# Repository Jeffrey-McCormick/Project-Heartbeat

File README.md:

Hello! Welcome to Project Heartbeat, my individual project for my ENGR 355 - Embedded System Design class.
This project's first revision is finished and turned in for credit. Later versions may appear as I have opportunity to expand this heartrate monitor's capabilities. I used KiCad and ARM Keil applications for designing and programming the board. 

I encourage you to read the Project Heartbeat Design Report to understand my design approach as well as what the functions of my code are for. 
Although, you should be able to read the comments in my code and understand what is happening. 

Here is what it looked like in KiCad and in reality.

The text I used was produced by ARM Education. Here is the Github resource: https://github.com/arm-education/Embedded-Systems-Fundamentals?tab=readme-ov-file

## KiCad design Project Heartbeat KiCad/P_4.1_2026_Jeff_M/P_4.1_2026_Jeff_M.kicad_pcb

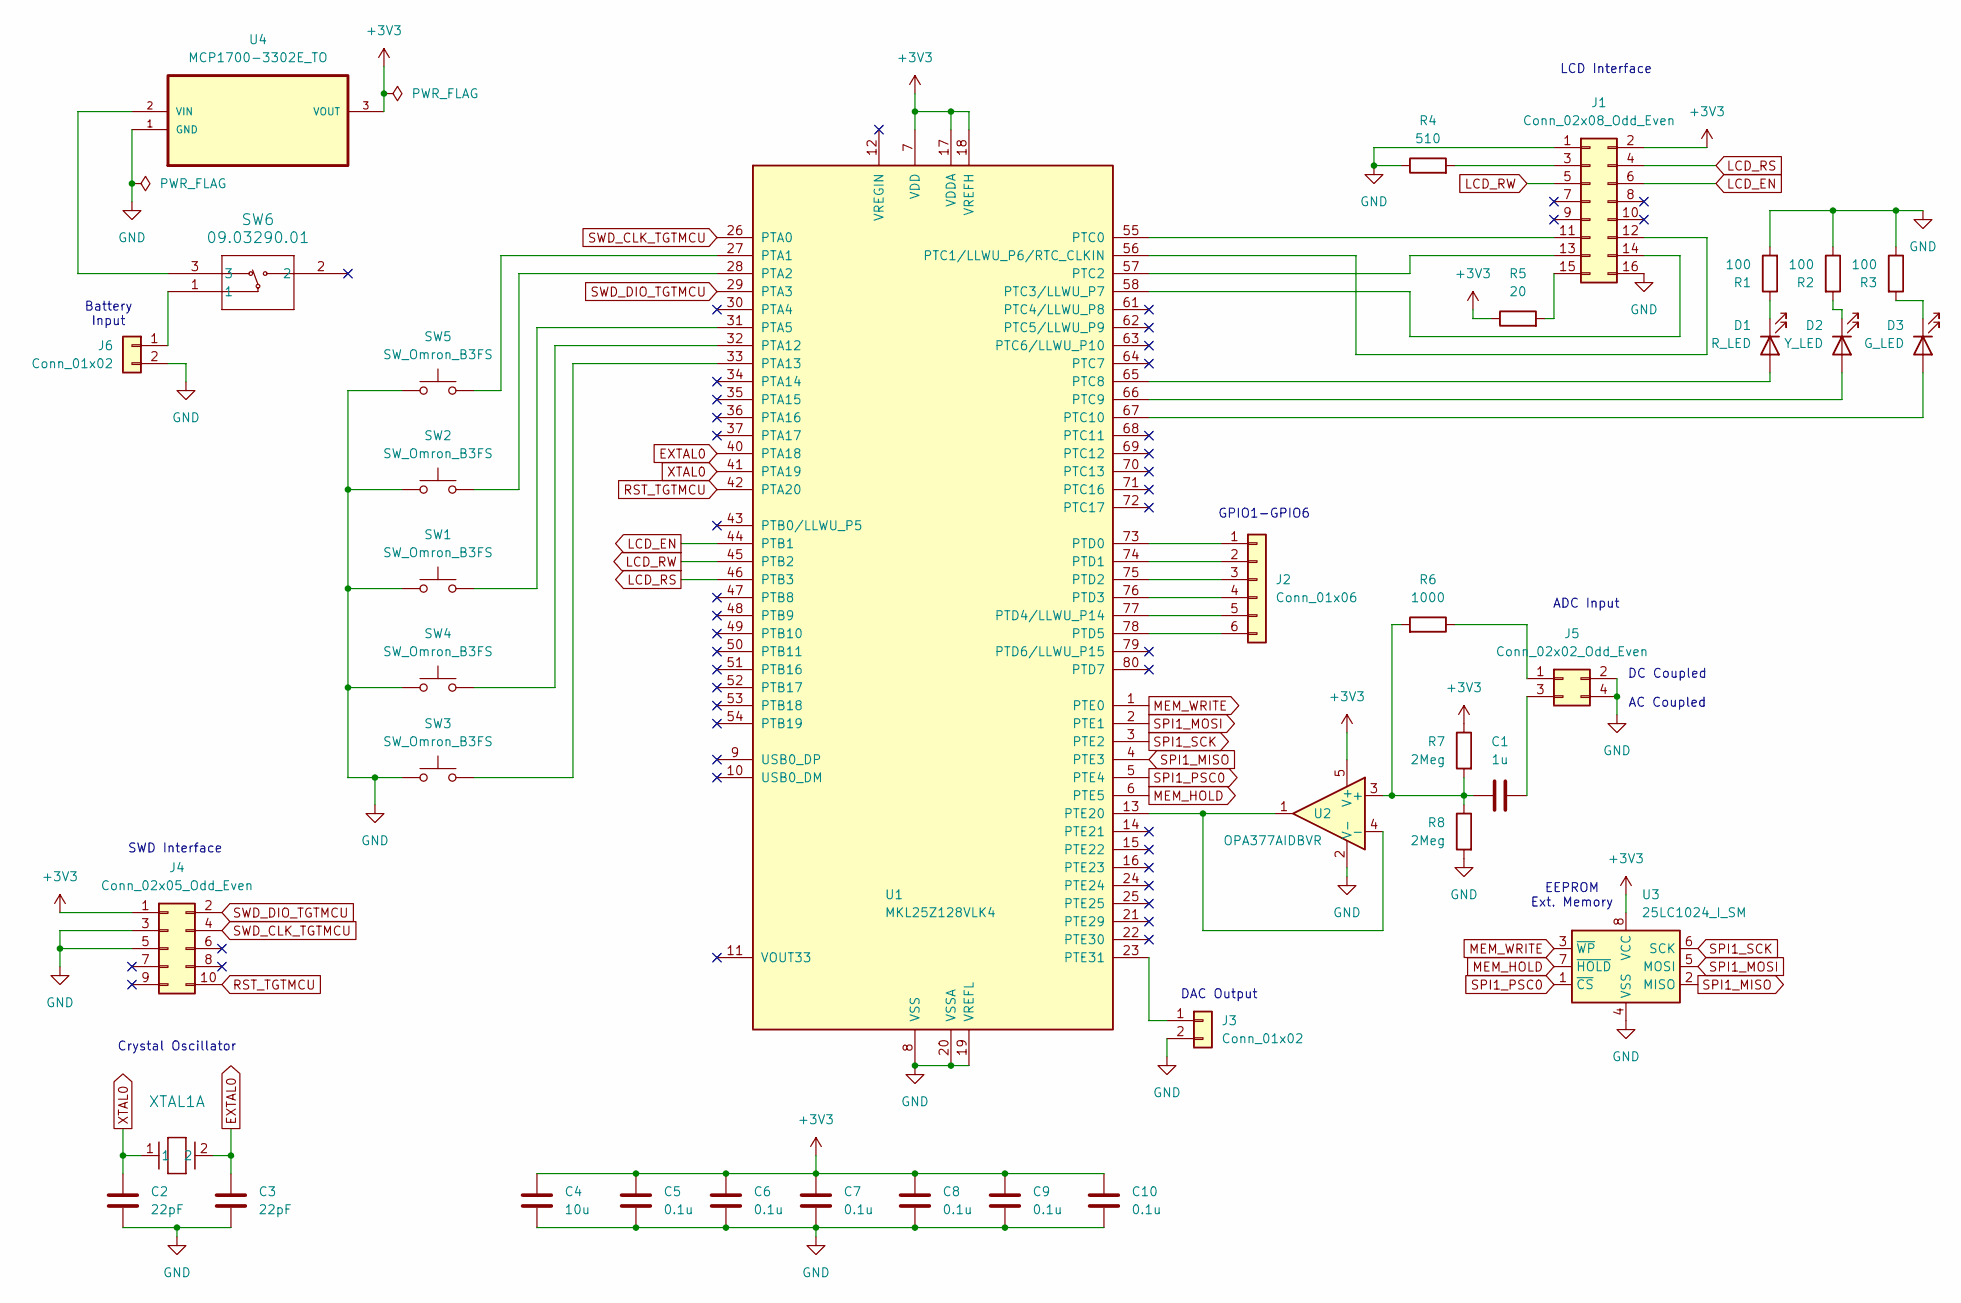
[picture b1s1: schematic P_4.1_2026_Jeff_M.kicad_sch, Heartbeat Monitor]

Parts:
C1: 1u; C_0805_2012Metric
C2, C3: 22pF; C_0805_2012Metric
C4: 10u; C_0805_2012Metric
C5, C6, C7, C8, C9, C10: 0.1u; C_0805_2012Metric
D1: R_LED; LED_1206_3216Metric
D2: Y_LED; LED_1206_3216Metric
D3: G_LED; LED_1206_3216Metric
J1: Conn_02x08_Odd_Even; PinHeader_2x08_P2.54mm_Vertical
J2: Conn_01x06; PinHeader_1x06_P2.54mm_Vertical
J3, J6: Conn_01x02; PinHeader_1x02_P2.54mm_Vertical
J4: Conn_02x05_Odd_Even; PinHeader_2x05_P1.27mm_Vertical
J5: Conn_02x02_Odd_Even; PinHeader_2x02_P2.54mm_Vertical
R1, R2, R3: 100; R_0805_2012Metric
R4: 510; R_0805_2012Metric
R5: 20; R_0805_2012Metric
R6: 1000; R_0805_2012Metric
R7, R8: 2Meg; R_0805_2012Metric
SW1, SW2, SW3, SW4, SW5: SW_Omron_B3FS; SW_SPST_Omron_B3FS-101xP
SW6: 09.03290.01; 09.03290_EAO
U1: MKL25Z128VLK4; LQFP-80_12x12mm_P0.5mm
U2: OPA377AIDBVR; SOT95P280X145-5N
U3: 25LC1024_I_SM; SOIC127P794X202-8N
U4: MCP1700-3302E_TO; TO127P254X495-3; MPN MCP1700-3302E/TO
XTAL1: ABM3-8.000MHZ-D2Y-T; XTAL_ABM3-8.000MHZ-D2Y-T_ABR

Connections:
+3V3: C4.1, C5.1, C6.1, C7.1, C8.1, C9.1, C10.1, J1.2, J4.1, R5.1, R7.1, U1.7 (VDD), U1.17 (VDDA), U1.18 (VREFH), U1.38 (VDD), U1.60 (VDD), U2.5 (V+), U3.8 (VCC), U4.3 (VOUT)
EXTAL0: C3.1, U1.40 (PTA18), XTAL1.2
GND: C2.2, C3.2, C4.2, C5.2, C6.2, C7.2, C8.2, C9.2, C10.2, J1.1, J1.16, J3.2, J4.3, J4.5, J5.2, J5.4, J6.2, R1.2, R2.1, R3.1, R4.1, R8.2, SW1.1, SW2.1, SW3.1, SW4.1, SW5.1, U1.8 (VSS), U1.19 (VREFL), U1.20 (VSSA), U1.39 (VSS), U1.59 (VSS), U2.2 (V-), U3.4 (VSS), U4.1 (GND)
LCD_EN: J1.6, U1.44 (PTB1)
LCD_RS: J1.4, U1.46 (PTB3)
LCD_RW: J1.5, U1.45 (PTB2)
MEM_HOLD: U1.6 (PTE5), U3.7 (~HOLD)
MEM_WRITE: U1.1 (PTE0), U3.3 (~WP)
unnamed: D1.2 (A), U1.65 (PTC8)
unnamed: D1.1 (K), R1.1
unnamed: D2.2 (A), U1.66 (PTC9)
unnamed: D2.1 (K), R2.2
unnamed: D3.2 (A), U1.67 (PTC10)
unnamed: D3.1 (K), R3.2
unnamed: J1.3, R4.2
unnamed: J1.11, U1.55 (PTC0)
unnamed: J1.12, U1.56 (PTC1/LLWU_P6/RTC_CLKIN)
unnamed: J1.13, U1.57 (PTC2)
unnamed: J1.14, U1.58 (PTC3/LLWU_P7)
unnamed: J1.15, R5.2
unnamed: J2.1, U1.73 (PTD0)
unnamed: J2.2, U1.74 (PTD1)
unnamed: J2.3, U1.75 (PTD2)
unnamed: J2.4, U1.76 (PTD3)
unnamed: J2.5, U1.77 (PTD4/LLWU_P14)
unnamed: J2.6, U1.78 (PTD5)
unnamed: J3.1, U1.23 (PTE31)
unnamed: J5.1, R6.1
unnamed: C1.1, J5.3
unnamed: J6.1, SW6.1
unnamed: SW5.2, U1.27 (PTA1)
unnamed: SW2.2, U1.28 (PTA2)
unnamed: SW1.2, U1.31 (PTA5)
unnamed: SW4.2, U1.32 (PTA12)
unnamed: SW3.2, U1.33 (PTA13)
unnamed: U1.13 (PTE20), U2.1, U2.4 (-)
unnamed: C1.2, R6.2, R7.2, R8.1, U2.3 (+)
unnamed: SW6.3, U4.2 (VIN)
RST_TGTMCU: J4.10, U1.42 (PTA20)
SPI1_MISO: U1.4 (PTE3), U3.2 (MISO)
SPI1_MOSI: U1.2 (PTE1), U3.5 (MOSI)
SPI1_PSC0: U1.5 (PTE4), U3.1 (~CS)
SPI1_SCK: U1.3 (PTE2), U3.6 (SCK)
SWD_CLK_TGTMCU: J4.4, U1.26 (PTA0)
SWD_DIO_TGTMCU: J4.2, U1.29 (PTA3)
XTAL0: C2.1, U1.41 (PTA19), XTAL1.1

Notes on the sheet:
DAC Output
GPIO1-GPIO6
SWD Interface
Crystal Oscillator
Battery Input
EEPROM Ext. Memory
LCD Interface
ADC Input
DC Coupled AC Coupled

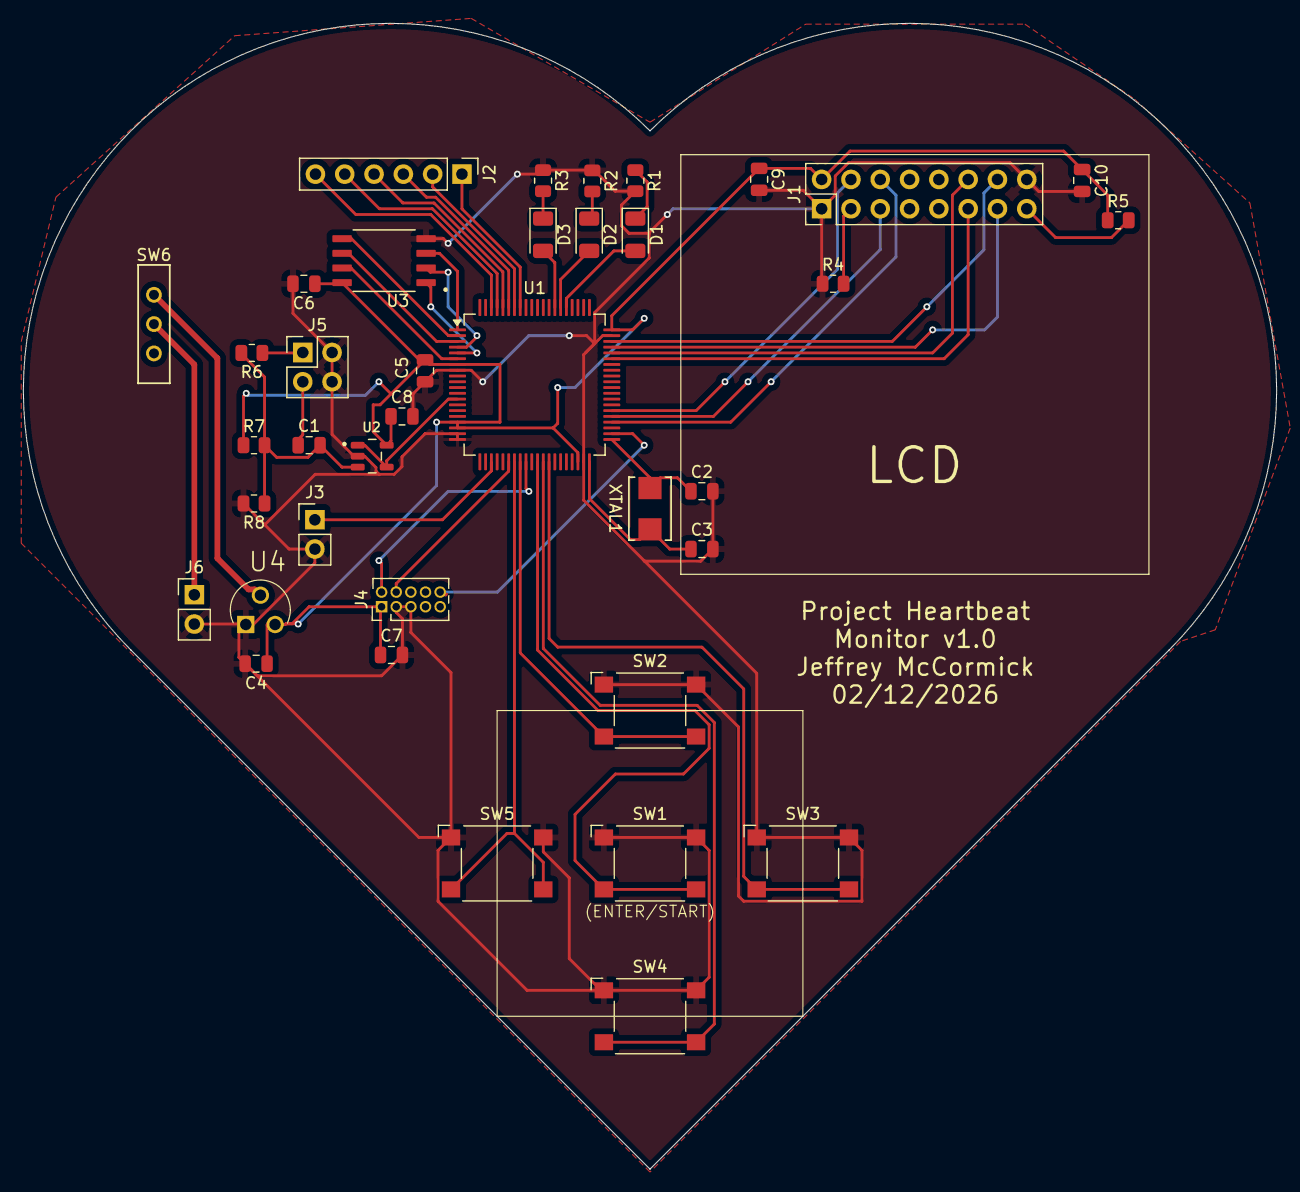
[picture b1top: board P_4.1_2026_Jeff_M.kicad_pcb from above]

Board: 2 copper layers, 108.6 x 99.3 mm, 38 parts (0 on the bottom side), 46 nets.

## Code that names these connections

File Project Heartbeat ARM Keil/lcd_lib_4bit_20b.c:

/*----------------------------------------------------------------------------*/
/*  LCD initialization and data transfer routines                             */
/*       4-bit bus version                                                    */
/*  Filename: lcd_lib_4bit_20b.c                                              */
/*  Author:   Larry Aamodt                                                    */
/*  Version:  1/25/19 written                                                 */
/*            1/28/19 updated                                                 */
/*            1/29/20 updated for wtr 2020 project                            */
/*            2/12/20 revised LCD control signal port & pins                  */
/*            3/10/21 added defines for cursor commands                       */
/*            1/19/22 updated comments re clock turn on. No code changes      */
/*  Compiler: Keil uVision5                                                   */
/*  Hardware: NXP Freedom board & a 2x8 or 2x16 LCD display w/parallel interfc*/
/*            PORT B  bits 1,2,3 used for control                             */
/*            PORT C  bits 0,1,2,3 used for data                              */
/*  Software note:  A software loop is used for time delay generation         */
/*        Port B and C clocks must be turned on before calling these routines */
/*  Function use:   call LCD_command to move the cursor, clear screen, etc.   */
/*                  call LCD_send_data to send one ASCII character code       */
/*----------------------------------------------------------------------------*/
#include <stdint.h>
#include <MKL25Z4.h>

#define LCD_EN              0x00000002    // PTB1 LCD enable 
#define LCD_RW              0x00000004    // PTB2 LCD read/write
#define LCD_RS              0x00000008    // PTB3 LCD RS
#define LCD_LOW4_MASK       0x0000000F    // low 4 bits of a command
#define LCD_UPPER4_MASK     0x000000F0    // upper 4 bits of a command
#define LCD_MASK            0x0000000F    // PortC bits 0-3
#define LCD_DATA_PINS       0x0000000F    // PortC LCD data pins
#define LCD_CNTRL_PINS      0x0000000E    // PortB LCD control pins

#define clear_screen 0x01
#define cursor_left 0x10
#define cursor_right 0x14
#define cursor_line1 0x80
#define cursor_line2 0xC0


/*----------------------------------------------------------------------------
  LCD functions 
 *----------------------------------------------------------------------------*/
void LCD_command(uint32_t command);       // use to send LCD commands
void LCD_send_data(uint32_t data);        // use to send one char to screen
void delayMs(uint32_t n);
void pulse_the_LCD_enable(void);
void LCD_init(void);

/*----------------------------------------------------------------------------
  Initialize the LCD in 4-bit bus mode.         L.Aamodt
 *----------------------------------------------------------------------------*/
void LCD_init(void)
{
  // Note: you need to turn on Port B and C clocks prior to calling this routine

	uint32_t k;

     // First set up bits in GPIO Port C used by the LCD
	for (k=0; k<4; k++) {                  // make ports GPIO
	PORTC->PCR[k] &= ~PORT_PCR_MUX_MASK;    // 4 LCD data bits
	PORTC->PCR[k] |= PORT_PCR_MUX(1);
	}
	
	for (k=1; k<4; k++) {                   // make ports GPIO
	PORTB->PCR[k] &= ~PORT_PCR_MUX_MASK;    //   LCD control 3-bits 
	PORTB->PCR[k] |= PORT_PCR_MUX(1);	
	}
	
	PTC->PDDR |= LCD_DATA_PINS;             // set ports to output
	PTB->PDDR |= LCD_CNTRL_PINS;

	PTB->PCOR = LCD_RW | LCD_RS | LCD_EN;   // clear R/W, RS, and EN	
		// Now initialize the LCD itself
	delayMs(00);
	PTC->PCOR = LCD_MASK;                   // clear output data bits to 0
	PTC->PSOR = (0x3);                   // put a wake-up value on bus
	delayMs(10);
	pulse_the_LCD_enable();
	delayMs(1);
	pulse_the_LCD_enable();
	delayMs(1);
	pulse_the_LCD_enable();
	delayMs(1);
	PTC->PCOR = LCD_MASK;                   // clear output data bits to 0
	PTC->PSOR = (0x2);                   // initialize to 4-bit bus mode
	delayMs(10);
	pulse_the_LCD_enable();
	LCD_command(0x28);                      // Set to 4-bit/2-line/5x7pixels
	LCD_command(0x10);                      // 
	LCD_command(0x0F);                      // Display on, cursor on and blink
	LCD_command(0x06);                      //
}
/*----------------------------------------------------------------------------
  Send a command to the LCD                      L.Aamodt
 *----------------------------------------------------------------------------*/
void LCD_command(uint32_t command)
{
	PTB->PCOR = LCD_RW | LCD_RS | LCD_EN;   // clear R/W, RS, and EN
	PTC->PCOR = LCD_MASK;                   // clear output data bits to 0
	PTC->PSOR = (command & LCD_UPPER4_MASK)>>4; // output upper 4 bits of command
	pulse_the_LCD_enable();
	PTC->PCOR = LCD_MASK;                   // clear output data bits
	PTC->PSOR = (command & LCD_LOW4_MASK);   // output lower 4 bits
	pulse_the_LCD_enable();
	if (command < 4)
		delayMs(3);                           // command 1 and 2 need 1.64ms
	else
		delayMs(1);                           // all others 40us
}
/*----------------------------------------------------------------------------
   Pulse the LCD enable line                    L.Aamodt
 *----------------------------------------------------------------------------*/
void pulse_the_LCD_enable(void)
{
	PTB->PSOR = LCD_EN;                     // assert enable
	delayMs(1);
	PTB->PCOR = LCD_EN;                     // de-assert enable
}

/*----------------------------------------------------------------------------
   Send data (one character, using ASCII code) to the LCD      L.Aamodt
 *----------------------------------------------------------------------------*/
void LCD_send_data(uint32_t data)
{
	PTB->PCOR = LCD_RW | LCD_EN;            // clear R/W, RS, and EN
	PTB->PSOR = LCD_RS;                     // set RS high
	PTC->PCOR = LCD_MASK;                   // clear output data bits to 0
	PTC->PSOR = (data & LCD_UPPER4_MASK)>>4;   // output upper 4 bits of command
	pulse_the_LCD_enable();
	PTC->PCOR = LCD_MASK;                   // clear output data bits
	PTC->PSOR = (data & LCD_LOW4_MASK);  // output lower 4 bits
	pulse_the_LCD_enable();
}
/*----------------------------------------------------------------------------
  Delay, used with the LCD routines.  Delay specified in units of milliseconds
      The inner loop max count should be 3500 for 20.97 MHZ system clock rate
      or 8000 for 48 MHZ system clock rate                      L.Aamodt
 *----------------------------------------------------------------------------*/
void delayMs(uint32_t n)
{
uint32_t i;
uint32_t j;
for(i=0; i < n; i++)
		for(j=0; j < 3500; j++) {}
}

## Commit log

2026-03-23 Add project files via upload
2026-03-23 Add project overview to README.md
    Added introductory information about Project Heartbeat, including project status and design report reference.
2026-03-23 Enhance README with project details and tools used
    Updated project description to include tools used for design and programming.
2026-03-23 Update README with ARM Education resource link
    Added a reference to ARM Education's GitHub resource.
2026-03-30 Add MIT License to the project
